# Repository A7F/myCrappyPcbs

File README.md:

# my crappy PCBs
these are some nice PCBs I designed for myself to make my life (and job) a little easier.

All the PCBs you see here are actually tested to be functional and working (produced by JLCPCB). However, I'm not an electrical engineer: I design PCBs as an hobby in my free time and I'm still learning, so please, if you find something off feel free to open a PR and contribute!

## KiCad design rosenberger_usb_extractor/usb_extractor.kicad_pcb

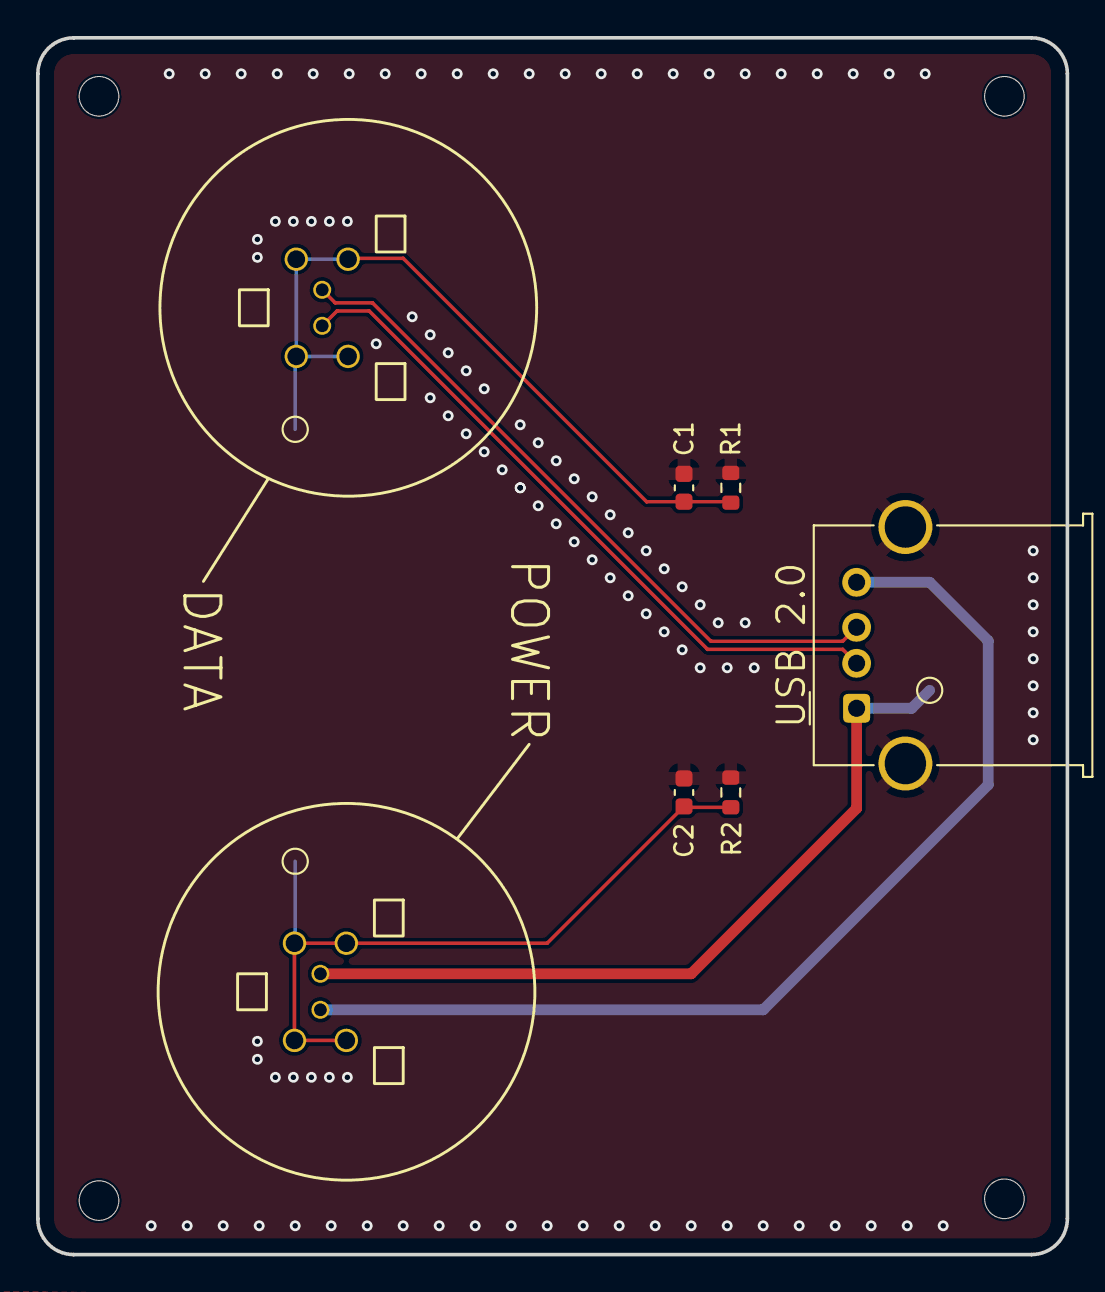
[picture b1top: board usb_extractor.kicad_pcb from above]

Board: 2 copper layers, 57.2 x 67.6 mm, 10 parts (0 on the bottom side), 7 nets.

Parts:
C1, C2: 100nF; C_0603_1608Metric
DATA: E6S14A-40MT5-A
POWER: E6S14A-40MT5-A
R1, R2: 0R; R_0603_1608Metric
TP1, TP2, TP3: TestPoint; TestPoint_Pad_D1.0mm
USB 2.0: USB_A; USB_A_Molex_67643_Horizontal

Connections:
/usb_DN: DATA.2, USB 2.0.2 (D-)
/usb_DP: DATA.1, USB 2.0.3 (D+)
/usb_gnd: POWER.2, USB 2.0.4 (GND)
/usb_vbus: POWER.1, TP3.1 (1_1), USB 2.0.1 (VBUS)
GND: C1.2, C2.2, R1.2, R2.2, USB 2.0.SH (Shield)
unnamed: C1.1, DATA.3 (shield), R1.1, TP2.1 (1_1)
unnamed: C2.1, POWER.3 (shield), R2.1, TP1.1 (1_1)

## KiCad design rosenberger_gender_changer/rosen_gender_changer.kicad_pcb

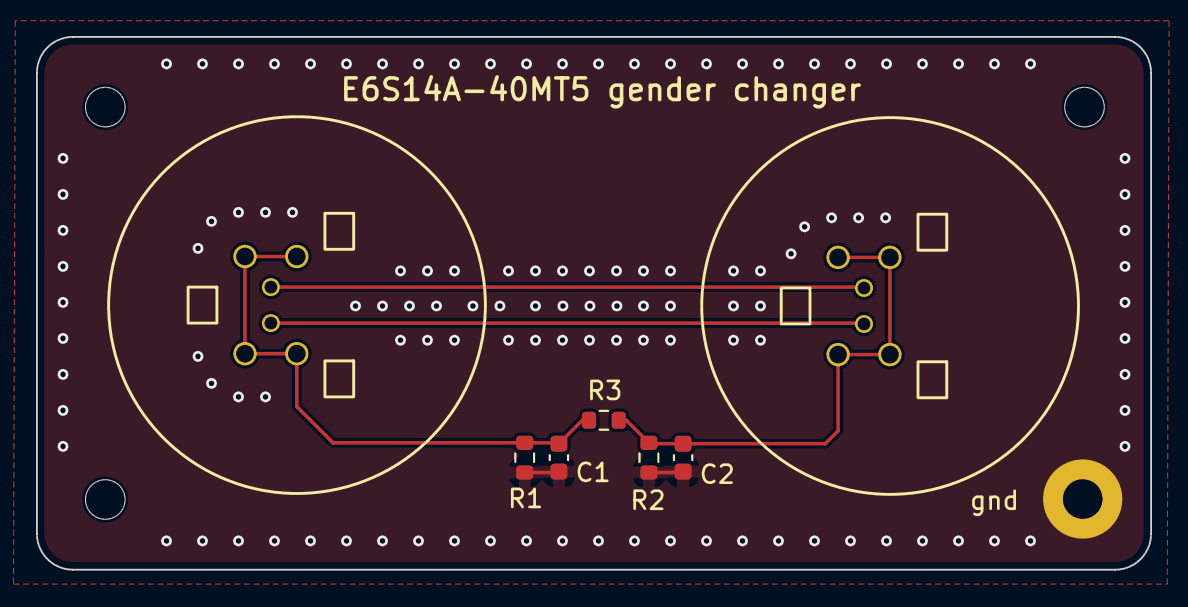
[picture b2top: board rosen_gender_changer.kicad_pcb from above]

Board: 2 copper layers, 61.9 x 29.6 mm, 8 parts (0 on the bottom side), 5 nets.

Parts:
C1, C2: 100nF; C_0603_1608Metric
E6S14A-40MT5-A1, E6S14A-40MT5-A2: E6S14A-40MT5-A
R1, R2, R3: 0R; R_0603_1608Metric
gnd: MountingHole_Pad; MountingHole_2.2mm_M2_Pad

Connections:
GND: C1.2, C2.2, R1.1, R2.2, gnd.1 (1_1)
unnamed: E6S14A-40MT5-A1.1, E6S14A-40MT5-A2.1
unnamed: E6S14A-40MT5-A1.2, E6S14A-40MT5-A2.2
unnamed: C1.1, E6S14A-40MT5-A1.3 (shield), R1.2, R3.2
unnamed: C2.1, E6S14A-40MT5-A2.3 (shield), R2.1, R3.1

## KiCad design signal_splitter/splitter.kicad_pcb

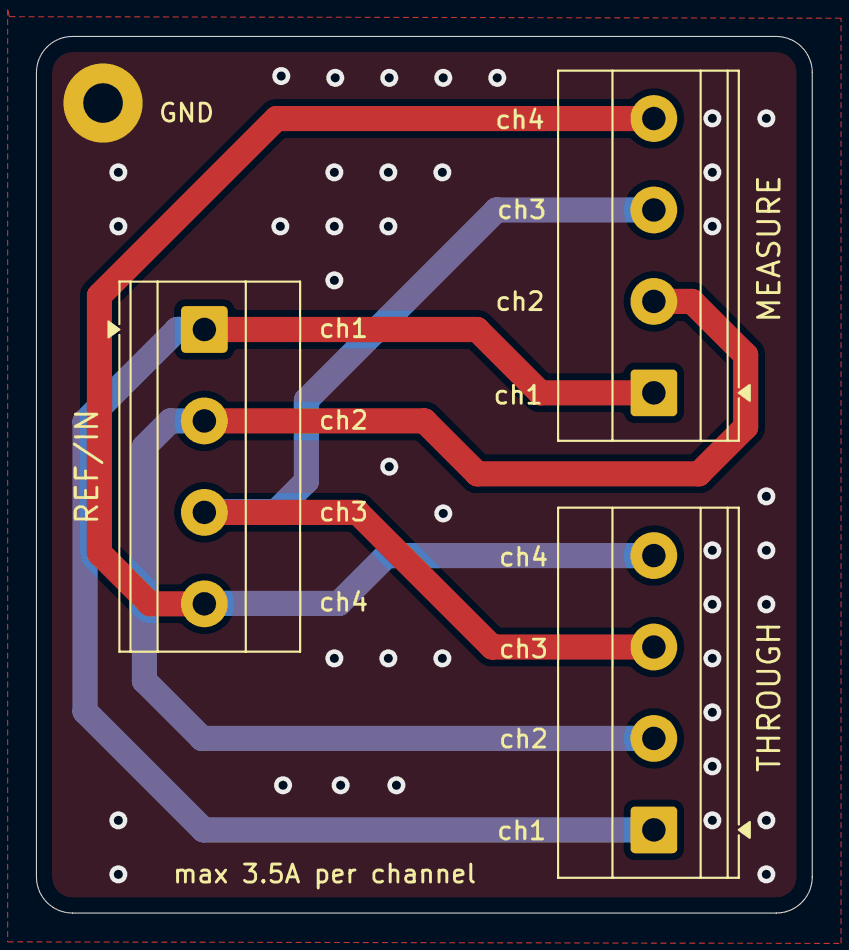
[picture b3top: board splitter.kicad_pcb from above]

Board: 2 copper layers, 43.1 x 48.7 mm, 4 parts (0 on the bottom side), 4 nets.

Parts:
GND: MountingHole_Pad; MountingHole_2.2mm_M2_Pad
MEASURE: Screw_Terminal_01x04; TerminalBlock_Phoenix_MKDS-1,5-4-5.08_1x04_P5.08mm_Horizont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
REF/IN: Screw_Terminal_01x04; TerminalBlock_Phoenix_MKDS-1,5-4-5.08_1x04_P5.08mm_Horizont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
THROUGH: Screw_Terminal_01x04; TerminalBlock_Phoenix_MKDS-1,5-4-5.08_1x04_P5.08mm_Horizont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

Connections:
unnamed: MEASURE.1, REF/IN.1, THROUGH.1
unnamed: MEASURE.2, REF/IN.2, THROUGH.2
unnamed: MEASURE.3, REF/IN.3, THROUGH.3
unnamed: MEASURE.4, REF/IN.4, THROUGH.4

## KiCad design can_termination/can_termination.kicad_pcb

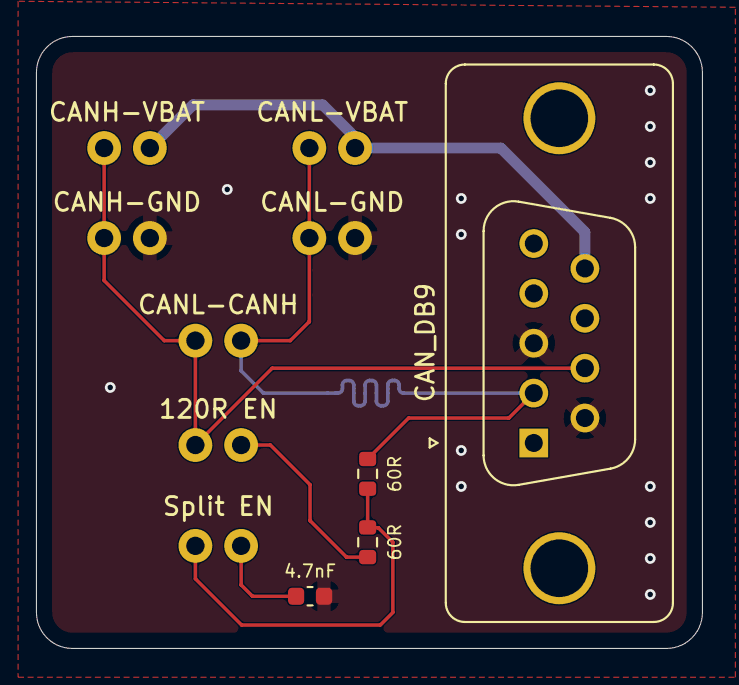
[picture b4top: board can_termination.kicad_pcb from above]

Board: 2 copper layers, 37.0 x 34.0 mm, 11 parts (0 on the bottom side), 7 nets.

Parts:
60R, 60R#2: 60R; R_0603_1608Metric
120R EN: Conn_01x02; 1x02_P2.54mm
C1: 4.7nF; C_0603_1608Metric
CANH-GND: Conn_01x02; 1x02_P2.54mm
CANH-VBAT: Conn_01x02; 1x02_P2.54mm
CANL-CANH: Conn_01x02; 1x02_P2.54mm
CANL-GND: Conn_01x02; 1x02_P2.54mm
CANL-VBAT: Conn_01x02; 1x02_P2.54mm
CAN_DB9: DE9_Pins_MountingHoles; DSUB-9_Pins_Vertical_P2.77x2.84mm_MountingHoles
Split_EN1: Conn_01x02; 1x02_P2.54mm

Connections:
CAN_H: 120R EN.1, CANH-GND.1, CANH-VBAT.1, CANL-CANH.1, CAN_DB9.7
CAN_L: 60R#2.1, CANL-CANH.2, CANL-GND.1, CANL-VBAT.1, CAN_DB9.2
GND: C1.2, CANH-GND.2, CANL-GND.2, CAN_DB9.3, CAN_DB9.6
unnamed: 60R.2, 120R EN.2
unnamed: 60R.1, 60R#2.2, Split_EN1.1
unnamed: C1.1, Split_EN1.2
VBAT: CANH-VBAT.2, CANL-VBAT.2, CAN_DB9.9
